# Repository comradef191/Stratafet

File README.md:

# Stratafet
One-Off board for Glizzy. Untested: Do not use.

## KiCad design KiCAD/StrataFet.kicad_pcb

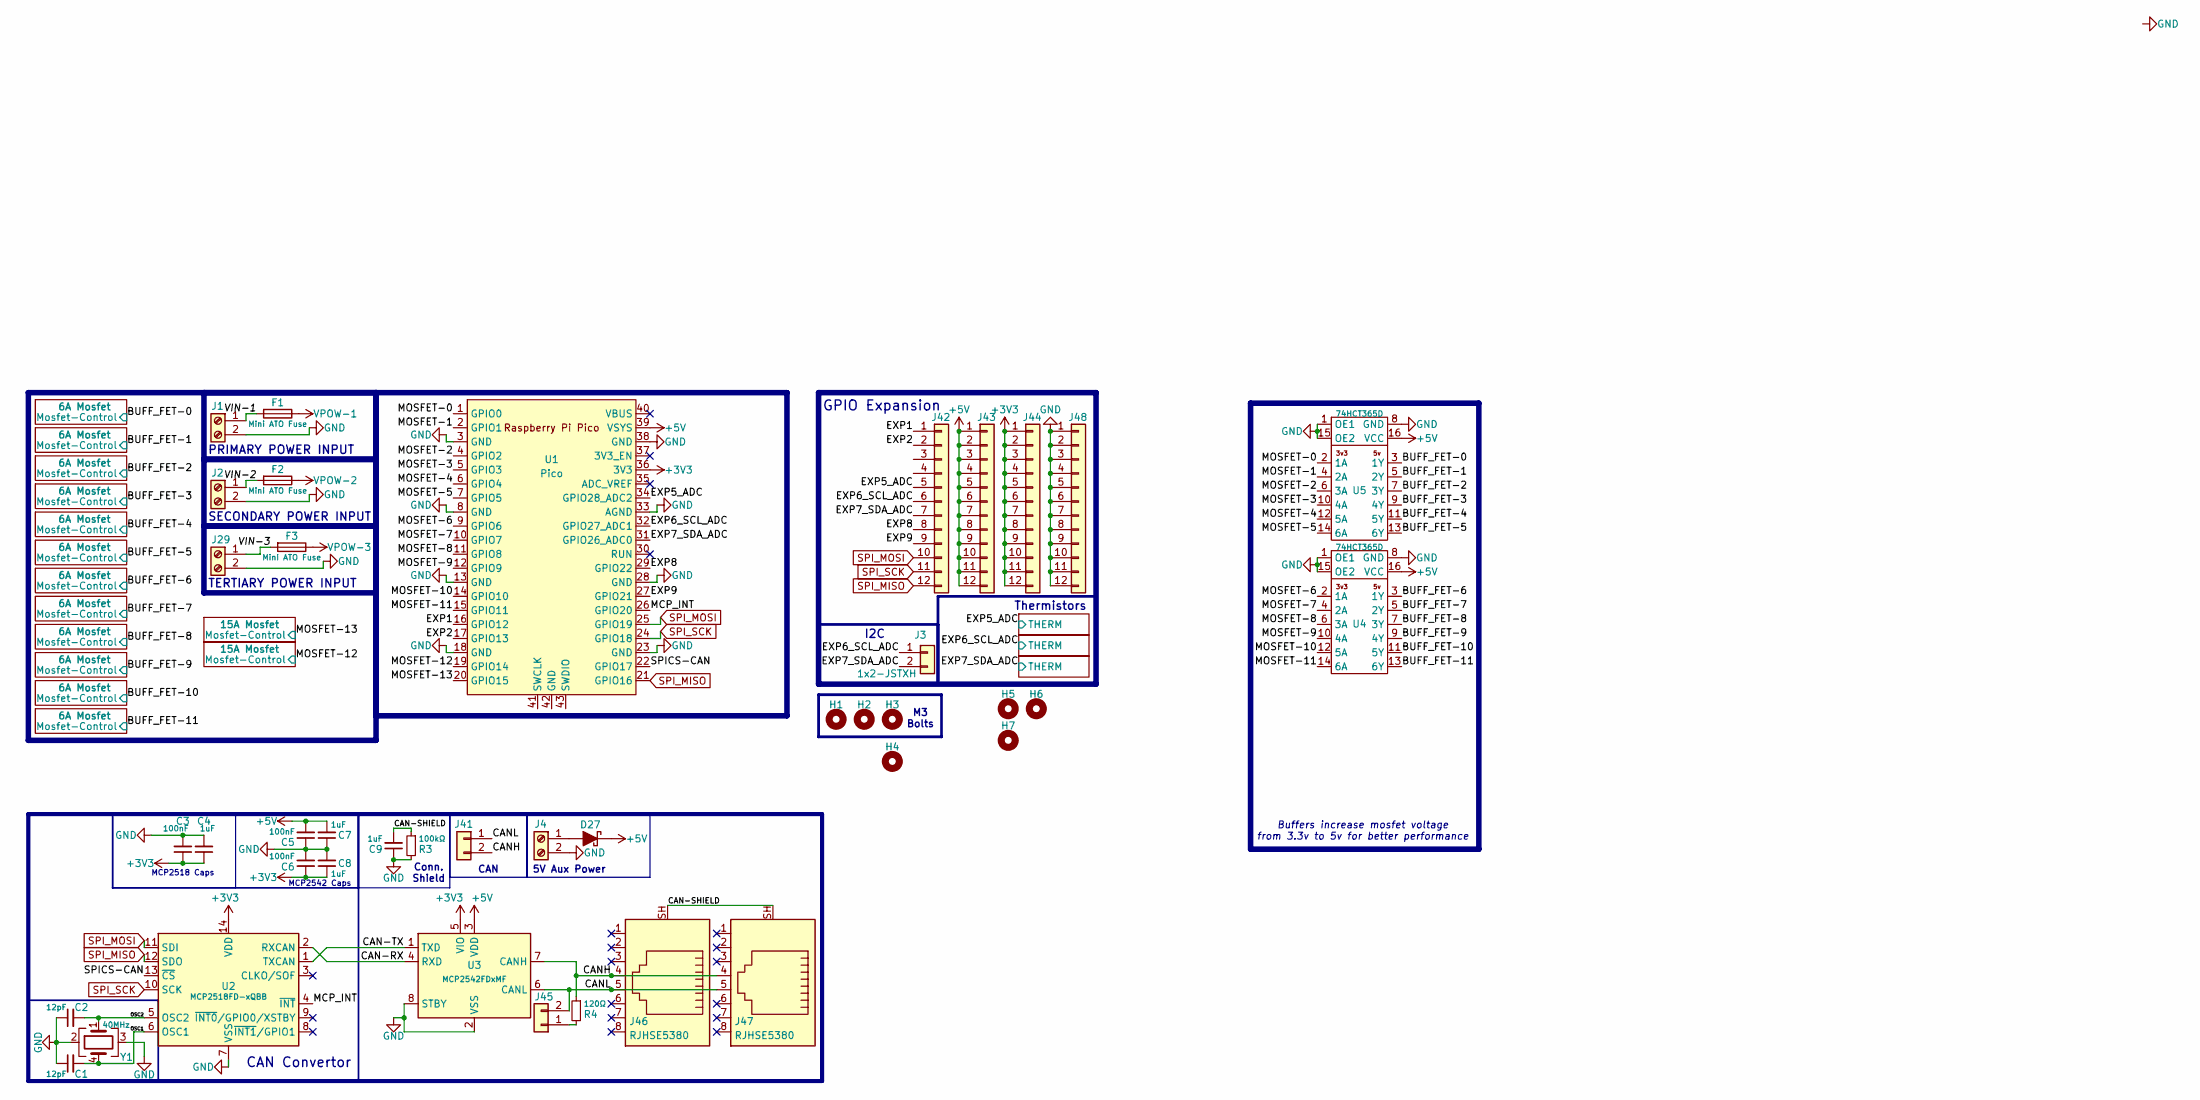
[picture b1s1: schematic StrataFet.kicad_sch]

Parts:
C1, C2: 12pF; C_0402_1005Metric; LCSC C696888
C3, C5, C6: 100nF; C_0402_1005Metric; LCSC C541464
C4, C7, C8, C9: 1uF; C_0402_1005Metric; LCSC C2887020
D27: MBR120VLSFT1G; D_SOD-123F; LCSC C891416
F1, F2, F3: Mini ATO Fuse; Fuseholder_Blade_Mini_Keystone_3568; Mouser 534-3568
H1, H2, H3, H4, H5, H6, H7: M3 Mounting Hole; M3 Mounting Hole ~ Classic
J1, J2, J29: Screw_Terminal_01x02; CONN-TH_HB9500M-9.5-2P; LCSC C601239
J3: 1x2-JSTXH; JST-XH_1x02-V ~ Custom; LCSC C5160911
J4: Screw_Terminal_01x02; TerminalBlock_Phoenix_MKDS-3-2-5.08_1x02_P5.08mm_Horizontal; LCSC C5188485
J41: 2.54-Header-1x2; JST_XH_B2B-XH-A_1x02_P2.50mm_Vertical
J42, J43, J44, J48: 2.54-Header-1x12; PinHeader_1x12_P2.54mm_Vertical
J45: 2.54-Header-1x2; PinHeader_1x02_P2.54mm_Vertical
J46, J47: RJHSE5380; RJ45_Amphenol_RJHSE5380; LCSC C464586
R3: 100kΩ; R_0402_1005Metric; LCSC C25741
R4: 120Ω; R_0402_1005Metric; LCSC C25079
U1: Pico; Socketed MCU - Pico
U2: MCP2518FD-xQBB; DFN-14-1EP_3x4.5mm_P0.65mm_EP1.65x4.25mm; LCSC C621395
U3: MCP2542FDxMF; DFN-8-1EP_3x3mm_P0.65mm_EP1.7x2.05mm; LCSC C635109
U4, U5: 74HCT365D; SOP-16_4.4x10.4mm_P1.27mm; LCSC C547597
Y1: 40MHz; Crystal_SMD_3225-4Pin_3.2x2.5mm; LCSC C5261245

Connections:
+3V3: C3.1, C4.1, C6.1, C8.1, J44.1, J44.2, J44.3, J44.4, J44.5, J44.6, J44.7, J44.8, J44.9, J44.10, J44.11, J44.12, U1.36 (3V3), U2.14 (VDD), U3.5 (VIO); also elsewhere on the board
+5V: C5.2, C7.2, D27.1 (K), J43.1, J43.2, J43.3, J43.4, J43.5, J43.6, J43.7, J43.8, J43.9, J43.10, J43.11, J43.12, U1.39 (VSYS), U3.3 (VDD), U4.16 (VCC), U5.16 (VCC); also elsewhere on the board
/BUFF_FET-0: U5.3 (1Y); also elsewhere on the board
/BUFF_FET-1: U5.5 (2Y); also elsewhere on the board
/BUFF_FET-2: U5.7 (3Y); also elsewhere on the board
/BUFF_FET-3: U5.9 (4Y); also elsewhere on the board
/BUFF_FET-4: U5.11 (5Y); also elsewhere on the board
/BUFF_FET-5: U5.13 (6Y); also elsewhere on the board
/BUFF_FET-6: U4.3 (1Y); also elsewhere on the board
/BUFF_FET-7: U4.5 (2Y); also elsewhere on the board
/BUFF_FET-8: U4.7 (3Y); also elsewhere on the board
/BUFF_FET-9: U4.9 (4Y); also elsewhere on the board
/BUFF_FET-10: U4.11 (5Y); also elsewhere on the board
/BUFF_FET-11: U4.13 (6Y); also elsewhere on the board
/CAN-RX: U2.2 (RXCAN), U3.4 (RXD)
/CAN-SHIELD: C9.2, J46.SH, J47.SH, R3.1
/CAN-TX: U2.1 (TXCAN), U3.1 (TXD)
/CANH: J41.2, J46.4, J47.4, R4.1, U3.7 (CANH)
/CANL: J41.1, J45.2, J46.5, J47.5, U3.6 (CANL)
/EXP1: J42.1, U1.16 (GPIO12)
/EXP2: J42.2, U1.17 (GPIO13)
/EXP5_ADC: J42.5, U1.34 (GPIO28_ADC2); also elsewhere on the board
/EXP6_SCL_ADC: J3.1, J42.6, U1.32 (GPIO27_ADC1); also elsewhere on the board
/EXP7_SDA_ADC: J3.2, J42.7, U1.31 (GPIO26_ADC0); also elsewhere on the board
/EXP8: J42.8, U1.29 (GPIO22)
/EXP9: J42.9, U1.27 (GPIO21)
/MCP_INT: U1.26 (GPIO20), U2.4 (~INT)
/MOSFET-0: U1.1 (GPIO0), U5.2 (1A)
/MOSFET-1: U1.2 (GPIO1), U5.4 (2A)
/MOSFET-2: U1.4 (GPIO2), U5.6 (3A)
/MOSFET-3: U1.5 (GPIO3), U5.10 (4A)
/MOSFET-4: U1.6 (GPIO4), U5.12 (5A)
/MOSFET-5: U1.7 (GPIO5), U5.14 (6A)
/MOSFET-6: U1.9 (GPIO6), U4.2 (1A)
/MOSFET-7: U1.10 (GPIO7), U4.4 (2A)
/MOSFET-8: U1.11 (GPIO8), U4.6 (3A)
/MOSFET-9: U1.12 (GPIO9), U4.10 (4A)
/MOSFET-10: U1.14 (GPIO10), U4.12 (5A)
/MOSFET-11: U1.15 (GPIO11), U4.14 (6A)
/MOSFET-12: U1.19 (GPIO14); also elsewhere on the board
/MOSFET-13: U1.20 (GPIO15); also elsewhere on the board
/OSC1: C1.2, U2.6 (OSC1), Y1.4
/OSC2: C2.2, U2.5 (OSC2), Y1.1
/SPICS-CAN: U1.22 (GPIO17), U2.13 (~CS)
/VIN-1: F1.2, J1.1
/VIN-2: F2.2, J2.1
/VIN-3: F3.2, J29.1
GND: C1.1, C2.1, C3.2, C4.2, C5.1, C6.2, C7.1, C8.2, C9.1, J1.2, J2.2, J4.2, J29.2, J48.1, J48.2, J48.3, J48.4, J48.5, J48.6, J48.7, J48.8, J48.9, J48.10, J48.11, J48.12, R3.2, U1.3 (GND), U1.8 (GND), U1.13 (GND), U1.18 (GND), U1.23 (GND), U1.28 (GND), U1.33 (AGND), U1.38 (GND), U2.7 (VSS), U2.15 (VSS), U3.2 (VSS), U3.8 (STBY), U3.9 (VSS), U4.1 (OE1), U4.8 (GND), U4.15 (OE2), U5.1 (OE1), U5.8 (GND), U5.15 (OE2), Y1.2, Y1.3; also elsewhere on the board
unnamed: D27.2 (A), J4.1
unnamed: J45.1, R4.2
SPI_MISO: J42.12, U1.21 (GPIO16), U2.12 (SDO)
SPI_MOSI: J42.10, U1.25 (GPIO19), U2.11 (SDI)
SPI_SCK: J42.11, U1.24 (GPIO18), U2.10 (SCK)
VPOW-1: F1.1; also elsewhere on the board
VPOW-2: F2.1; also elsewhere on the board
VPOW-3: F3.1; also elsewhere on the board

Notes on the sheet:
MCP2518 Caps
M3 Bolts
CAN
TERTIARY POWER INPUT
SECONDARY POWER INPUT
GPIO Expansion
Buffers increase mosfet voltage from 3.3v to 5v for better performance
5V Aux Power
CAN Convertor
Conn. Shield
PRIMARY POWER INPUT
Thermistors
I2C
MCP2542 Caps

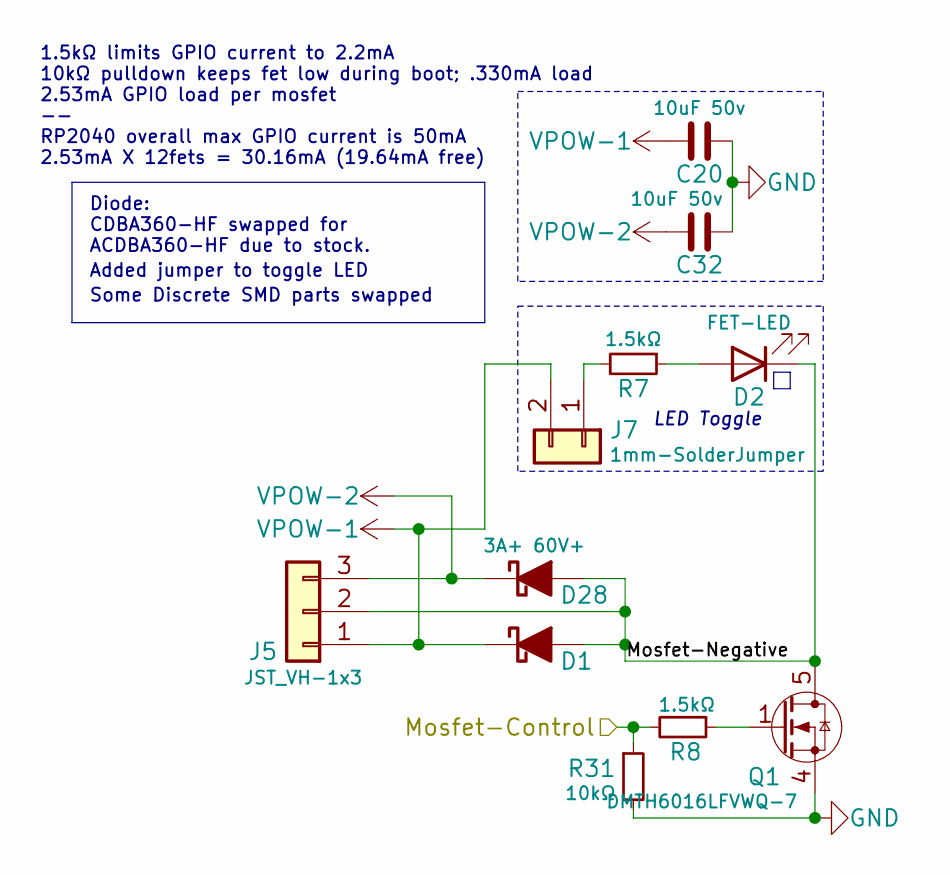
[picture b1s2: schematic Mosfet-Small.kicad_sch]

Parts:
C20, C32: 10uF 50v; C_1206_3216Metric; Part Number CL31A106KBHNNNE; LCSC C13585
D1, D28: 3A+ 60V+; D_SMA; LCSC C3019735
D2: FET-LED; LED_0603_1608Metric; LCSC C965799
J5: JST_VH-1x3; JST_VH_B3P-VH_1x03_P3.96mm_Vertical
J7: 1mm-SolderJumper; SolderJumper-2_P1.3mm_Bridged_Pad1.0x1.5mm
Q1: DMTH6016LFVWQ-7; Diodes_PowerDI3333-8_ThermalVias; Mouser 621-DMTH6016LFVWQ-7
R7, R8: 1.5kΩ; R_0402_1005Metric; LCSC C25867
R31: 10kΩ; R_0402_1005Metric; LCSC C25744

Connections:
/BUFF_FET-0: R8.2, R31.1; also elsewhere on the board
/Mosfet-Small/Mosfet-Negative: D1.2 (A), D2.1 (K), D28.2 (A), J5.2, Q1.5 (D)
GND: C20.2, C32.2, Q1.2 (S), Q1.3 (S), Q1.4 (S), R31.2; also elsewhere on the board
unnamed: D2.2 (A), R7.1
unnamed: J7.1, R7.2
unnamed: Q1.1 (G), R8.1
VPOW-1: C20.1, D1.1 (K), J5.1, J7.2; also elsewhere on the board
VPOW-2: C32.1, D28.1 (K), J5.3; also elsewhere on the board

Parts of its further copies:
C21, C22, C23, C24, C25, C26, C27, C28, C29, C30, C31, C33, C34, C35, C36, C37, C38, C39, C40, C41, C42, C43: 10uF 50v; C_1206_3216Metric; Part Number CL31A106KBHNNNE; LCSC C13585
D3, D5, D7, D9, D11, D13, D15, D17, D19, D21, D23, D29, D30, D31, D32, D33, D34, D35, D36, D37, D38, D39: 3A+ 60V+; D_SMA; LCSC C3019735
D4, D6, D8, D10, D12, D14, D16, D18, D20, D22, D24: FET-LED; LED_0603_1608Metric; LCSC C965799
J6, J8, J9, J11, J12, J14, J15, J17, J18, J20, J21: JST_VH-1x3; JST_VH_B3P-VH_1x03_P3.96mm_Vertical
J10, J13, J16, J19, J22, J25, J28, J31, J34, J37, J40: 1mm-SolderJumper; SolderJumper-2_P1.3mm_Bridged_Pad1.0x1.5mm
Q2, Q3, Q4, Q5, Q6, Q7, Q8, Q9, Q10, Q11, Q12: DMTH6016LFVWQ-7; Diodes_PowerDI3333-8_ThermalVias; Mouser 621-DMTH6016LFVWQ-7
R9, R10, R11, R12, R13, R14, R15, R16, R17, R18, R19, R20, R21, R22, R23, R24, R25, R26, R27, R28, R29, R30: 1.5kΩ; R_0402_1005Metric; LCSC C25867
R32, R33, R34, R35, R36, R37, R38, R39, R40, R41, R42: 10kΩ; R_0402_1005Metric; LCSC C25744

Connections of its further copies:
/BUFF_FET-1: R10.2, R32.1; also elsewhere on the board
/BUFF_FET-2: R12.2, R33.1; also elsewhere on the board
/BUFF_FET-3: R14.2, R34.1; also elsewhere on the board
/BUFF_FET-4: R16.2, R35.1; also elsewhere on the board
/BUFF_FET-5: R18.2, R36.1; also elsewhere on the board
/BUFF_FET-6: R20.2, R37.1; also elsewhere on the board
/BUFF_FET-7: R22.2, R38.1; also elsewhere on the board
/BUFF_FET-8: R24.2, R39.1; also elsewhere on the board
/BUFF_FET-9: R26.2, R40.1; also elsewhere on the board
/BUFF_FET-10: R28.2, R41.1; also elsewhere on the board
/BUFF_FET-11: R30.2, R42.1; also elsewhere on the board
/Mosfet-Small1/Mosfet-Negative: D3.2 (A), D4.1 (K), D29.2 (A), J6.2, Q2.5 (D)
/Mosfet-Small2/Mosfet-Negative: D5.2 (A), D6.1 (K), D30.2 (A), J8.2, Q3.5 (D)
/Mosfet-Small3/Mosfet-Negative: D7.2 (A), D8.1 (K), D31.2 (A), J9.2, Q4.5 (D)
/Mosfet-Small4/Mosfet-Negative: D9.2 (A), D10.1 (K), D32.2 (A), J11.2, Q5.5 (D)
/Mosfet-Small5/Mosfet-Negative: D11.2 (A), D12.1 (K), D33.2 (A), J12.2, Q6.5 (D)
/Mosfet-Small6/Mosfet-Negative: D13.2 (A), D14.1 (K), D34.2 (A), J14.2, Q7.5 (D)
/Mosfet-Small7/Mosfet-Negative: D15.2 (A), D16.1 (K), D35.2 (A), J15.2, Q8.5 (D)
/Mosfet-Small8/Mosfet-Negative: D17.2 (A), D18.1 (K), D36.2 (A), J17.2, Q9.5 (D)
/Mosfet-Small9/Mosfet-Negative: D19.2 (A), D20.1 (K), D37.2 (A), J18.2, Q10.5 (D)
/Mosfet-Small10/Mosfet-Negative: D21.2 (A), D22.1 (K), D38.2 (A), J20.2, Q11.5 (D)
/Mosfet-Small11/Mosfet-Negative: D23.2 (A), D24.1 (K), D39.2 (A), J21.2, Q12.5 (D)
GND: C21.2, C22.2, C23.2, C24.2, C25.2, C26.2, C27.2, C28.2, C29.2, C30.2, C31.2, C33.2, C34.2, C35.2, C36.2, C37.2, C38.2, C39.2, C40.2, C41.2, C42.2, C43.2, Q2.2 (S), Q2.3 (S), Q2.4 (S), Q3.2 (S), Q3.3 (S), Q3.4 (S), Q4.2 (S), Q4.3 (S), Q4.4 (S), Q5.2 (S), Q5.3 (S), Q5.4 (S), Q6.2 (S), Q6.3 (S), Q6.4 (S), Q7.2 (S), Q7.3 (S), Q7.4 (S), Q8.2 (S), Q8.3 (S), Q8.4 (S), Q9.2 (S), Q9.3 (S), Q9.4 (S), Q10.2 (S), Q10.3 (S), Q10.4 (S), Q11.2 (S), Q11.3 (S), Q11.4 (S), Q12.2 (S), Q12.3 (S), Q12.4 (S), R32.2, R33.2, R34.2, R35.2, R36.2, R37.2, R38.2, R39.2, R40.2, R41.2, R42.2; also elsewhere on the board
unnamed: D4.2 (A), R9.1
unnamed: D6.2 (A), R11.1
unnamed: D8.2 (A), R13.1
unnamed: D10.2 (A), R15.1
unnamed: D12.2 (A), R17.1
unnamed: D14.2 (A), R19.1
unnamed: D16.2 (A), R21.1
unnamed: D18.2 (A), R23.1
unnamed: D20.2 (A), R25.1
unnamed: D22.2 (A), R27.1
unnamed: D24.2 (A), R29.1
unnamed: J10.1, R9.2
unnamed: J13.1, R11.2
unnamed: J16.1, R13.2
unnamed: J19.1, R15.2
unnamed: J22.1, R17.2
unnamed: J25.1, R19.2
unnamed: J28.1, R21.2
unnamed: J31.1, R23.2
unnamed: J34.1, R25.2
unnamed: J37.1, R27.2
unnamed: J40.1, R29.2
unnamed: Q2.1 (G), R10.1
unnamed: Q3.1 (G), R12.1
unnamed: Q4.1 (G), R14.1
unnamed: Q5.1 (G), R16.1
unnamed: Q6.1 (G), R18.1
unnamed: Q7.1 (G), R20.1
unnamed: Q8.1 (G), R22.1
unnamed: Q9.1 (G), R24.1
unnamed: Q10.1 (G), R26.1
unnamed: Q11.1 (G), R28.1
unnamed: Q12.1 (G), R30.1
VPOW-1: C21.1, C22.1, C23.1, C24.1, C25.1, C26.1, C27.1, C28.1, C29.1, C30.1, C31.1, D3.1 (K), D5.1 (K), D7.1 (K), D9.1 (K), D11.1 (K), D13.1 (K), D15.1 (K), D17.1 (K), D19.1 (K), D21.1 (K), D23.1 (K), J6.1, J8.1, J9.1, J10.2, J11.1, J12.1, J13.2, J14.1, J15.1, J16.2, J17.1, J18.1, J19.2, J20.1, J21.1, J22.2, J25.2, J28.2, J31.2, J34.2, J37.2, J40.2; also elsewhere on the board
VPOW-2: C33.1, C34.1, C35.1, C36.1, C37.1, C38.1, C39.1, C40.1, C41.1, C42.1, C43.1, D29.1 (K), D30.1 (K), D31.1 (K), D32.1 (K), D33.1 (K), D34.1 (K), D35.1 (K), D36.1 (K), D37.1 (K), D38.1 (K), D39.1 (K), J6.3, J8.3, J9.3, J11.3, J12.3, J14.3, J15.3, J17.3, J18.3, J20.3, J21.3; also elsewhere on the board

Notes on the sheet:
1.5kΩ limits GPIO current to 2.2mA 10kΩ pulldown keeps fet low during boot; .330mA load 2.53mA GPIO load per mosfet -- RP2040 overall max GPIO current is 50mA 2.53mA X 12fets = 30.16mA (19.64mA free)
Added jumper to toggle LED
Some Discrete SMD parts swapped
Diode: CDBA360-HF swapped for ACDBA360-HF due to stock.
LED Toggle

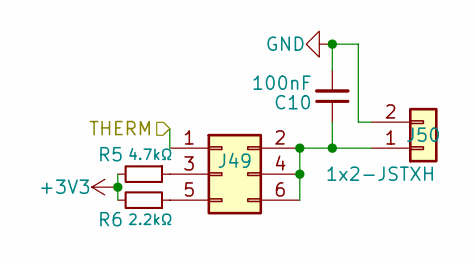
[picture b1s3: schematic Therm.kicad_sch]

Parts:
C10: 100nF; C_0402_1005Metric; LCSC C541464
J49: Conn_02x03_Odd_Even; PinHeader_2x03_P2.54mm_Vertical
J50: 1x2-JSTXH; JST-XH_1x02-V ~ Custom; LCSC C5160911
R5: 4.7kΩ; R_0402_1005Metric; LCSC C25900
R6: 2.2kΩ; R_0402_1005Metric; LCSC C25879

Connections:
+3V3: R5.2, R6.2; also elsewhere on the board
/EXP6_SCL_ADC: J49.1; also elsewhere on the board
GND: C10.2, J50.2; also elsewhere on the board
unnamed: C10.1, J49.2, J49.4, J49.6, J50.1
unnamed: J49.3, R5.1
unnamed: J49.5, R6.1

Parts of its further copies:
C11, C12: 100nF; C_0402_1005Metric; LCSC C541464
J51, J53: Conn_02x03_Odd_Even; PinHeader_2x03_P2.54mm_Vertical
J52, J54: 1x2-JSTXH; JST-XH_1x02-V ~ Custom; LCSC C5160911
R43, R45: 4.7kΩ; R_0402_1005Metric; LCSC C25900
R44, R46: 2.2kΩ; R_0402_1005Metric; LCSC C25879

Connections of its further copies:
+3V3: R43.2, R44.2, R45.2, R46.2; also elsewhere on the board
/EXP5_ADC: J51.1; also elsewhere on the board
/EXP7_SDA_ADC: J53.1; also elsewhere on the board
GND: C11.2, C12.2, J52.2, J54.2; also elsewhere on the board
unnamed: C11.1, J51.2, J51.4, J51.6, J52.1
unnamed: J51.3, R43.1
unnamed: J51.5, R44.1
unnamed: C12.1, J53.2, J53.4, J53.6, J54.1
unnamed: J53.3, R45.1
unnamed: J53.5, R46.1

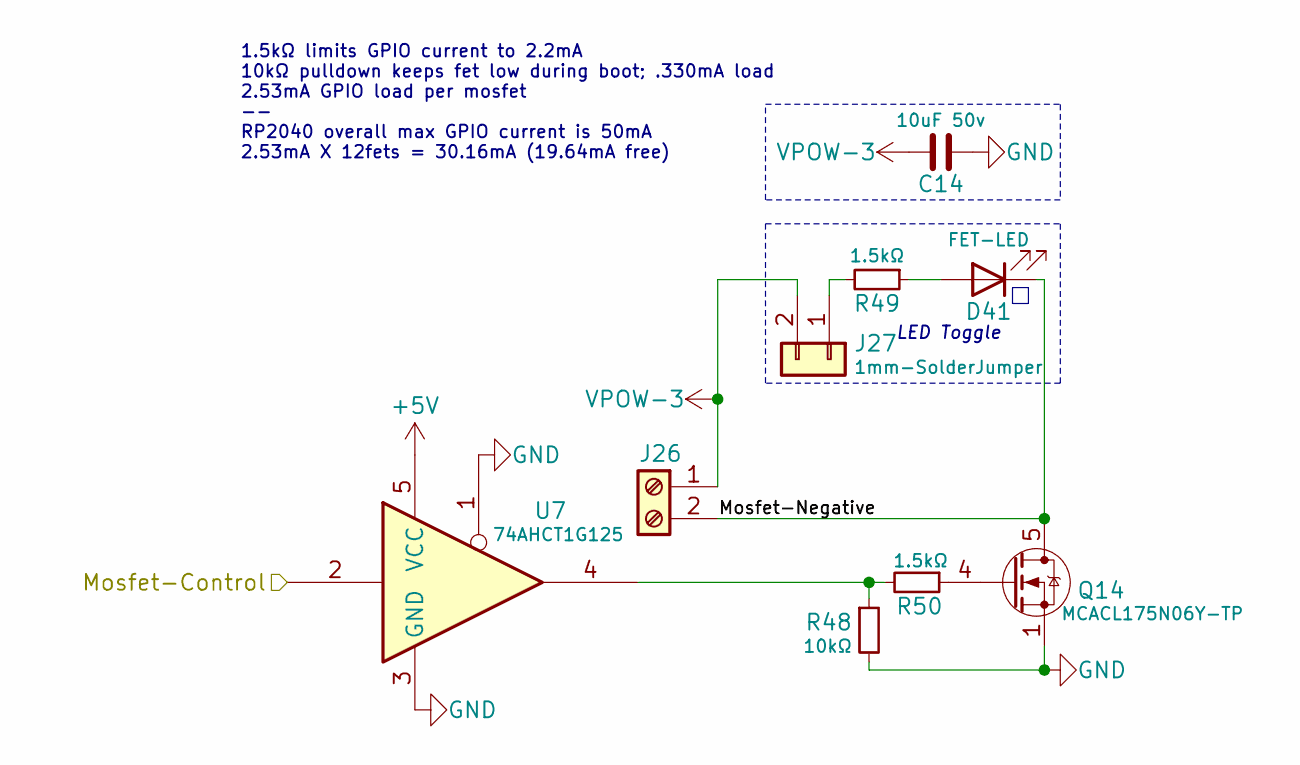
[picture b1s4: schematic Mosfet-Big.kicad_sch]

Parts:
C14: 10uF 50v; C_1206_3216Metric; Part Number CL31A106KBHNNNE; LCSC C13585
D41: FET-LED; LED_0603_1608Metric; LCSC C965799
J26: Screw_Terminal_01x02; TerminalBlock_Phoenix_MKDS-3-2-5.08_1x02_P5.08mm_Horizontal; LCSC C5188485
J27: 1mm-SolderJumper; SolderJumper-2_P1.3mm_Bridged_Pad1.0x1.5mm
Q14: MCACL175N06Y-TP; POWERDFN_DFN5060; Part Number MCACL175N06Y-TP; Mouser 833-MCACL175N06Y-TP
R48: 10kΩ; R_0402_1005Metric; LCSC C25744
R49, R50: 1.5kΩ; R_0402_1005Metric; LCSC C25867
U7: 74AHCT1G125; SOT-353_SC-70-5; LCSC C151417

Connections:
+5V: U7.5 (VCC); also elsewhere on the board
/MOSFET-12: U7.2; also elsewhere on the board
/Mosfet-Big1/Mosfet-Negative: D41.1 (K), J26.2, Q14.5 (D)
GND: C14.2, Q14.1 (S), Q14.2 (S), Q14.3 (S), R48.2, U7.1, U7.3 (GND); also elsewhere on the board
unnamed: D41.2 (A), R49.1
unnamed: J27.1, R49.2
unnamed: Q14.4 (G), R50.1
unnamed: R48.1, R50.2, U7.4
VPOW-3: C14.1, J26.1, J27.2; also elsewhere on the board

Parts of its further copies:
C13: 10uF 50v; C_1206_3216Metric; Part Number CL31A106KBHNNNE; LCSC C13585
D40: FET-LED; LED_0603_1608Metric; LCSC C965799
J23: Screw_Terminal_01x02; TerminalBlock_Phoenix_MKDS-3-2-5.08_1x02_P5.08mm_Horizontal; LCSC C5188485
J24: 1mm-SolderJumper; SolderJumper-2_P1.3mm_Bridged_Pad1.0x1.5mm
Q13: MCACL175N06Y-TP; POWERDFN_DFN5060; Part Number MCACL175N06Y-TP; Mouser 833-MCACL175N06Y-TP
R1: 10kΩ; R_0402_1005Metric; LCSC C25744
R2, R47: 1.5kΩ; R_0402_1005Metric; LCSC C25867
U6: 74AHCT1G125; SOT-353_SC-70-5; LCSC C151417

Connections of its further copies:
+5V: U6.5 (VCC); also elsewhere on the board
/MOSFET-13: U6.2; also elsewhere on the board
/Mosfet-Big/Mosfet-Negative: D40.1 (K), J23.2, Q13.5 (D)
GND: C13.2, Q13.1 (S), Q13.2 (S), Q13.3 (S), R1.2, U6.1, U6.3 (GND); also elsewhere on the board
unnamed: D40.2 (A), R2.1
unnamed: J24.1, R2.2
unnamed: Q13.4 (G), R47.1
unnamed: R1.1, R47.2, U6.4
VPOW-3: C13.1, J23.1, J24.2; also elsewhere on the board

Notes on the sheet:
LED Toggle
1.5kΩ limits GPIO current to 2.2mA 10kΩ pulldown keeps fet low during boot; .330mA load 2.53mA GPIO load per mosfet -- RP2040 overall max GPIO current is 50mA 2.53mA X 12fets = 30.16mA (19.64mA free)

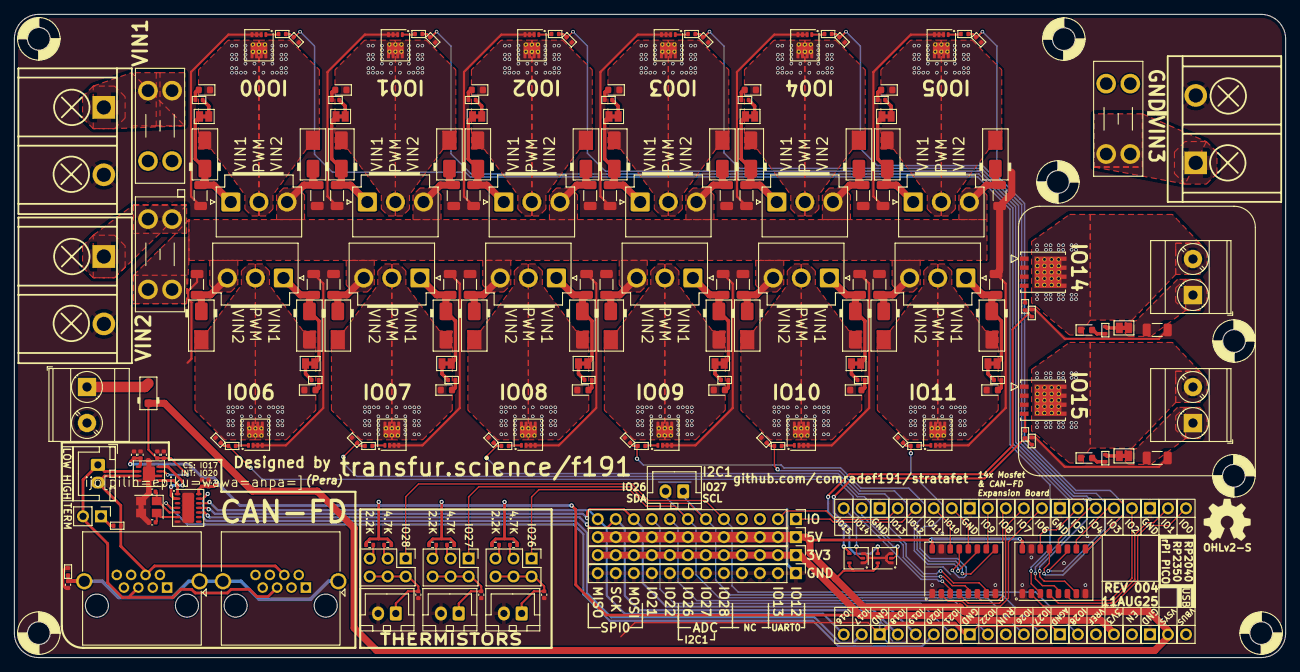
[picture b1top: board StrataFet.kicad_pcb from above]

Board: 2 copper layers, 179.2 x 90.7 mm, 206 parts (0 on the bottom side), 123 nets.

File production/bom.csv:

Designator,Footprint,Quantity,Value,LCSC Part #
"C1, C2",0402,2,12pF,C696888
"C10, C11, C12, C3, C5, C6",0402,6,100nF,C541464
"C13, C14, C20, C21, C22, C23, C24, C25, C26, C27, C28, C29, C30, C31, C32, C33, C34, C35, C36, C37, C38, C39, C40, C41, C42, C43",1206,26,10uF 50v,C13585
"C4, C7, C8, C9",0402,4,1uF,C2887020
"D1, D11, D13, D15, D17, D19, D21, D23, D28, D29, D3, D30, D31, D32, D33, D34, D35, D36, D37, D38, D39, D5, D7, D9",D_SMA,24,3A+ 60V+,C3019735
"D10, D12, D14, D16, D18, D2, D20, D22, D24, D4, D40, D41, D6, D8",0603,14,FET-LED,C965799
D27,D_SOD-123F,1,MBR120VLSFT1G,C891416
"F1, F2, F3",Fuseholder_Blade_Mini_Keystone_3568,3,Mini ATO Fuse,
"J1, J2, J29",CONN-TH_HB9500M-9.5-2P,3,Screw_Terminal_01x02,C601239
"J10, J13, J16, J19, J22, J24, J25, J27, J28, J31, J34, J37, J40, J7",SolderJumper-2_P1.3mm_Bridged_Pad1.0x1.5mm,14,1mm-SolderJumper,
"J11, J12, J14, J15, J17, J18, J20, J21, J5, J6, J8, J9",JST_VH_B3P-VH_1x03_P3.96mm_Vertical,12,JST_VH-1x3,
"J23, J26, J4",TerminalBlock_Phoenix_MKDS-3-2-5.08_1x02_P5.08mm_Horizontal,3,Screw_Terminal_01x02,C5188485
"J3, J50, J52, J54",JST-XH_1x02-V ~ Custom,4,1x2-JSTXH,C5160911
J41,JST_XH_B2B-XH-A_1x02_P2.50mm_Vertical,1,2.54-Header-1x2,
"J42, J43, J44, J48",PinHeader_1x12_P2.54mm_Vertical,4,2.54-Header-1x12,
J45,PinHeader_1x02_P2.54mm_Vertical,1,2.54-Header-1x2,
"J46, J47",RJ45_Amphenol_RJHSE5380,2,RJHSE5380,C464586
"J49, J51, J53",PinHeader_2x03_P2.54mm_Vertical,3,Conn_02x03_Odd_Even,
"Q1, Q10, Q11, Q12, Q2, Q3, Q4, Q5, Q6, Q7, Q8, Q9",Diodes_PowerDI3333-8_ThermalVias,12,DMTH6016LFVWQ-7,
"Q13, Q14",POWERDFN_DFN5060,2,MCACL175N06Y-TP,
"R1, R31, R32, R33, R34, R35, R36, R37, R38, R39, R40, R41, R42, R48",0402,14,10kΩ,C25744
"R10, R11, R12, R13, R14, R15, R16, R17, R18, R19, R2, R20, R21, R22, R23, R24, R25, R26, R27, R28, R29, R30, R47, R49, R50, R7, R8, R9",0402,28,1.5kΩ,C25867
R3,0402,1,100kΩ,C25741
R4,0402,1,120Ω,C25079
"R43, R45, R5",0402,3,4.7kΩ,C25900
"R44, R46, R6",0402,3,2.2kΩ,C25879
U1,Socketed MCU - Pico,1,Pico,
U2,DFN-14-1EP_3x4.5mm_P0.65mm_EP1.65x4.25mm,1,MCP2518FD-xQBB,C621395
U3,DFN-8-1EP_3x3mm_P0.65mm_EP1.7x2.05mm,1,MCP2542FDxMF,C635109
"U4, U5",SOP-16_4.4x10.4mm_P1.27mm,2,74HCT365D,C547597
"U6, U7",SOT-353_SC-70-5,2,74AHCT1G125,C151417
Y1,Crystal_SMD_3225-4Pin_3.2x2.5mm,1,40MHz,C5261245

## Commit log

2025-11-13 Add Files
